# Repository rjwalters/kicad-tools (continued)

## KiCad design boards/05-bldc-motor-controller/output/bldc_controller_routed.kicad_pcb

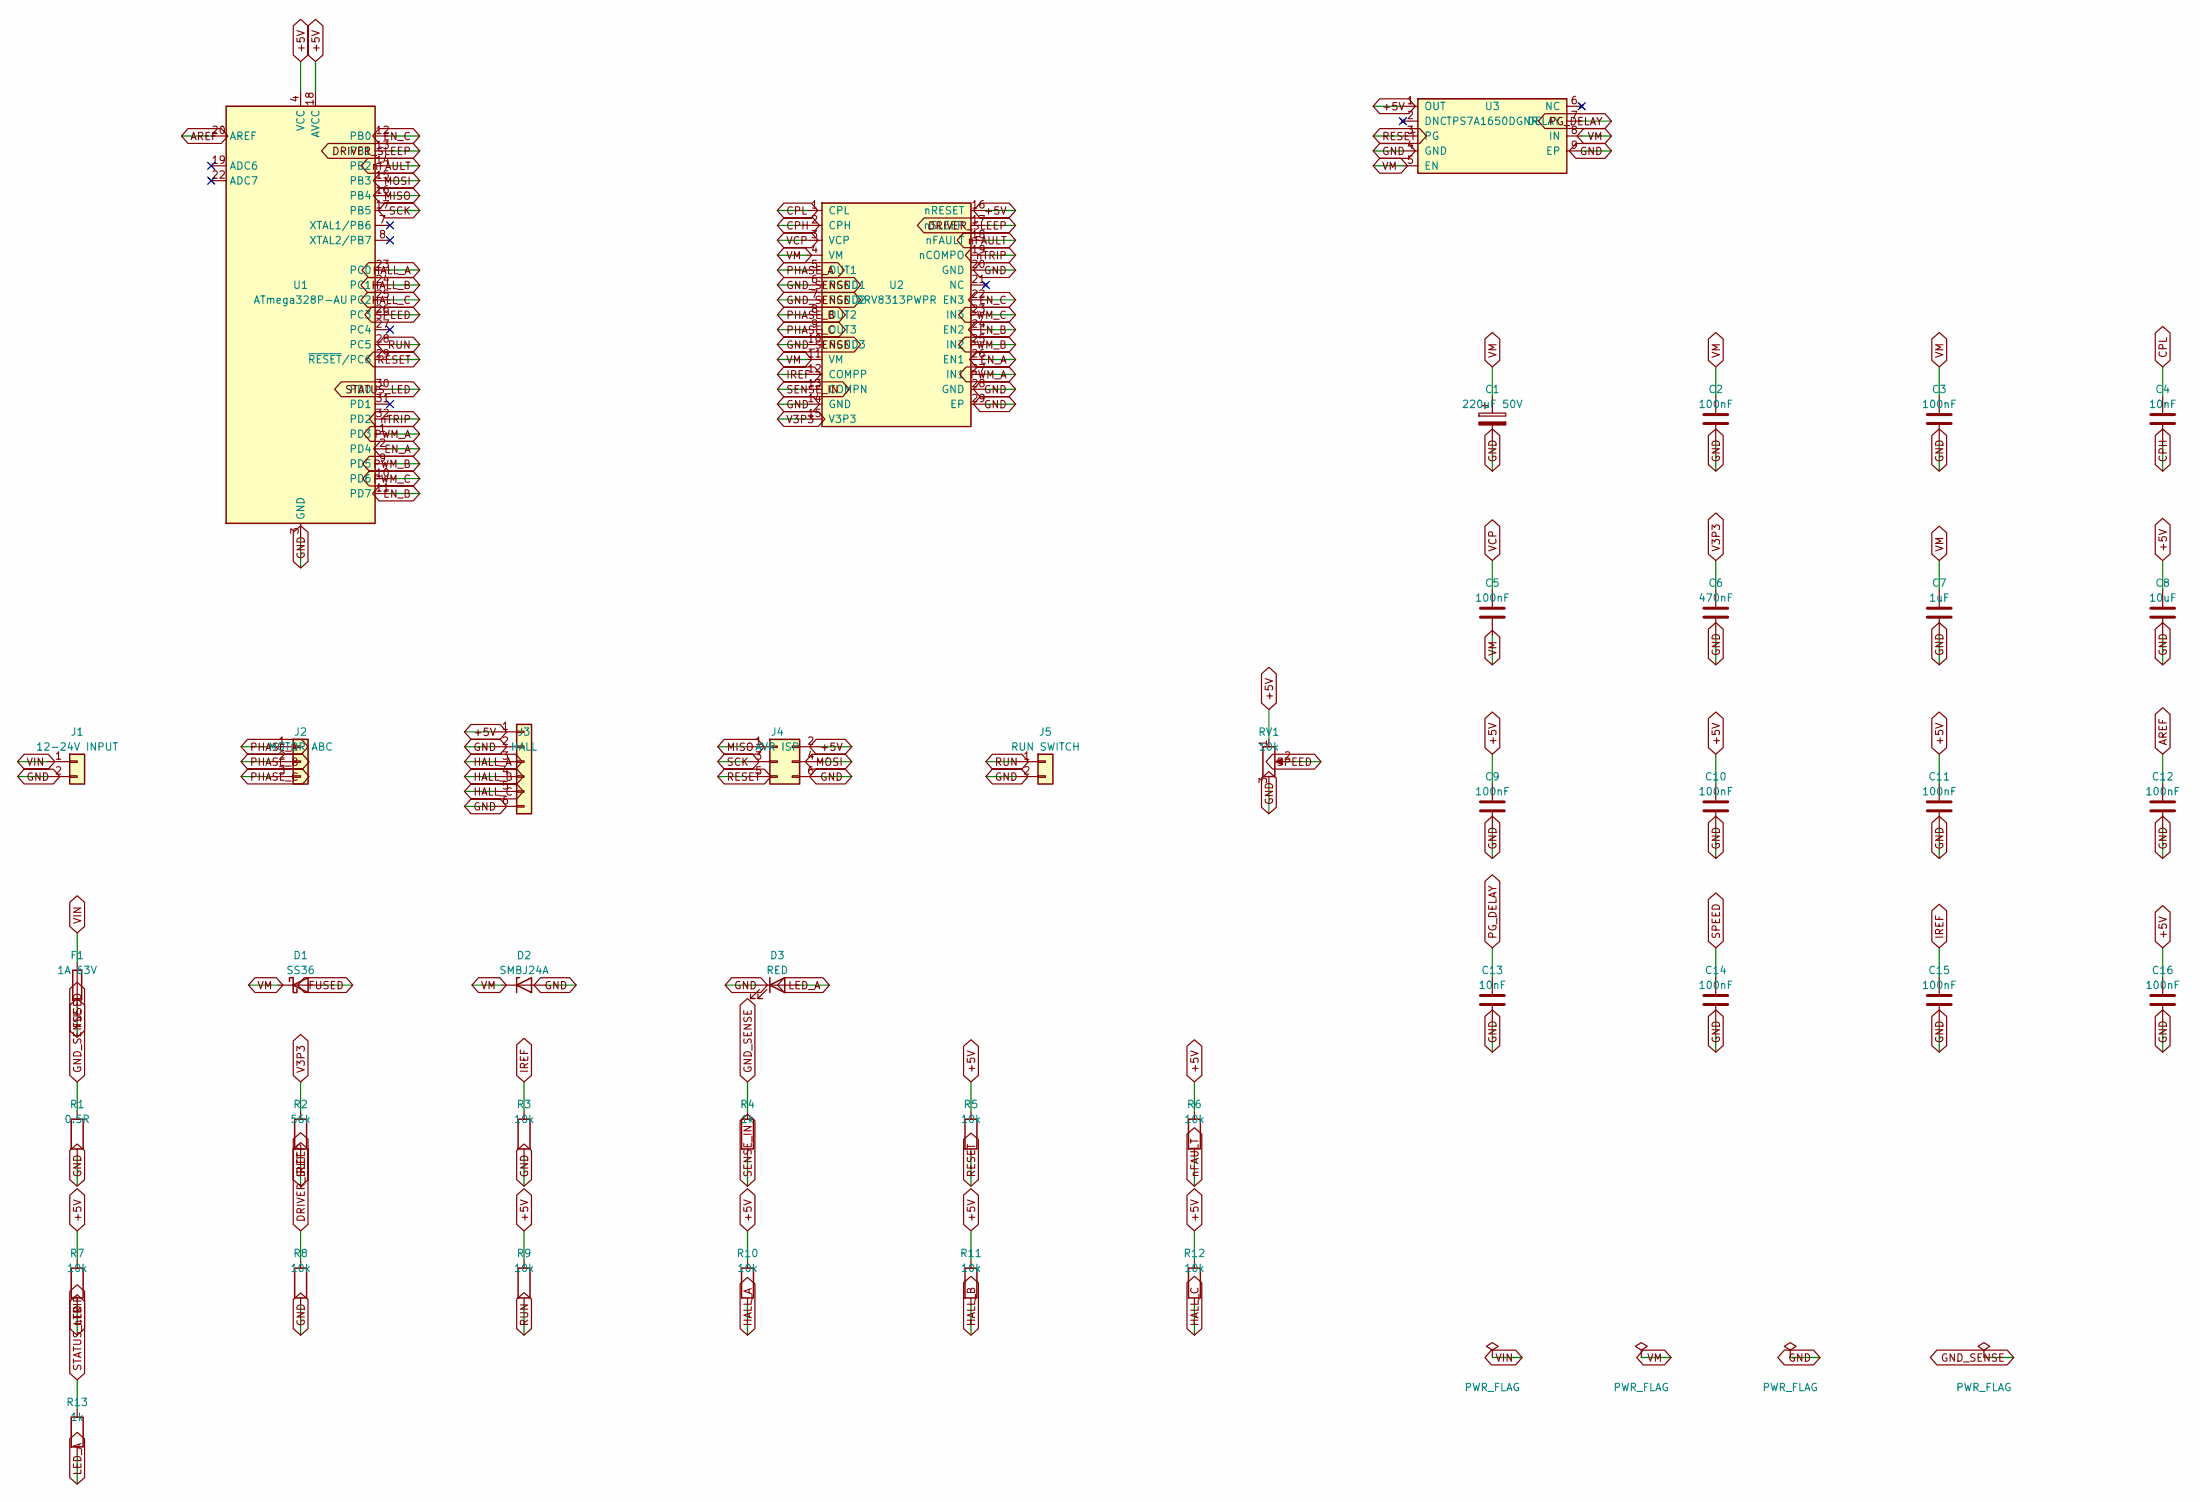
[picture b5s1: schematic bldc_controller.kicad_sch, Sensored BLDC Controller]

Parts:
C1: 220uF 50V; CP_Elec_8x10.5_PolarityMark; MPN EEEFT1H221AP; LCSC C178594
C2, C3, C5, C9, C10, C11, C12, C14, C15, C16: 100nF; C_0805_2012Metric; MPN CC0805KRX7R9BB104; LCSC C49678
C4, C13: 10nF; C_0805_2012Metric; MPN CL21B103KBANNNC; LCSC C1710
C6: 470nF; C_0805_2012Metric; MPN CL21B474KBFNNNE; LCSC C13967
C7: 1uF; C_0805_2012Metric; MPN CL21B105KBFNNNE; LCSC C28323
C8: 10uF; C_0805_2012Metric; MPN CL21A106KAYNNNE; LCSC C15850
D1: SS36; D_SMA; MPN SS36; LCSC C16015
D2: SMBJ24A; D_SMB; MPN SMBJ24A; LCSC C224017
D3: RED; LED_0805_2012Metric; MPN NCD0805R1; LCSC C84256
F1: 1A 63V; Fuse_1206_3216Metric; MPN SF-1206S100-2; LCSC C3167176
J1: 12-24V INPUT; PinHeader_1x02_P2.54mm_Vertical; MPN ZX-PZ2.54-1-2PZZ; LCSC C7501260
J2: MOTOR ABC; PinHeader_1x03_P2.54mm_Vertical; MPN 2.54-1*3P; LCSC C49257
J3: HALL; PinHeader_1x06_P2.54mm_Vertical; MPN 2.54-1*6P; LCSC C37208
J4: AVR ISP; PinHeader_2x03_P2.54mm_Vertical; MPN 2.54-2*3P; LCSC C65114
J5: RUN SWITCH; PinHeader_1x02_P2.54mm_Vertical; MPN ZX-PZ2.54-1-2PZZ; LCSC C7501260
R1: 0.5R; R_2512_6332Metric; MPN WSL2512R5000FEA; LCSC C511023
R2: 56k; R_0805_2012Metric; MPN 0805W8F5602T5E; LCSC C17756
R3, R5, R6, R7, R8, R9, R10, R11, R12: 10k; R_0805_2012Metric; MPN 0805W8F1002T5E; LCSC C17414
R4, R13: 1k; R_0805_2012Metric; MPN 0805W8F1001T5E; LCSC C17513
RV1: 10k; Potentiometer_Bourns_3296W_Vertical; MPN 3296W-1-103LF; LCSC C34846
U1: ATmega328P-AU; TQFP-32_7x7mm_P0.8mm; MPN ATMEGA328P-AU; LCSC C14877
U2: DRV8313PWPR; TI_PWP0028C_EP3.4x9.7_Mask3.1x5.18_ThermalVias; MPN DRV8313PWPR; LCSC C92482
U3: TPS7A1650DGNR; HVSSOP-8-1EP_3x3mm_P0.65mm_EP1.57x1.89mm_ThermalVias; MPN TPS7A1650DGNR; LCSC C468238

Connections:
+5V: C8.1, C9.1, C10.1, C11.1, C16.1, J3.1, J4.2, R5.1, R6.1, R7.1, R9.1, R10.1, R11.1, R12.1, RV1.1, U1.4 (VCC), U1.6 (VCC), U1.18 (AVCC), U2.16 (nRESET), U3.1 (OUT)
AREF: C12.1, U1.20 (AREF)
CPH: C4.2, U2.2 (CPH)
CPL: C4.1, U2.1 (CPL)
DRIVER_SLEEP: R8.1, U1.13 (PB1), U2.17 (nSLEEP)
EN_A: U1.2 (PD4), U2.26 (EN1)
EN_B: U1.11 (PD7), U2.24 (EN2)
EN_C: U1.12 (PB0), U2.22 (EN3)
FUSED: D1.2 (A), F1.2
HALL_A: J3.3, R10.2, U1.23 (PC0)
HALL_B: J3.4, R11.2, U1.24 (PC1)
HALL_C: J3.5, R12.2, U1.25 (PC2)
IREF: C15.1, R2.2, R3.1, U2.12 (COMPP)
LED_A: D3.2 (A), R13.2
MISO: J4.1, U1.16 (PB4)
MOSI: J4.4, U1.15 (PB3)
PG_DELAY: C13.1, U3.7 (DELAY)
PHASE_A: J2.1, U2.5 (OUT1)
PHASE_B: J2.2, U2.8 (OUT2)
PHASE_C: J2.3, U2.9 (OUT3)
PWM_A: U1.1 (PD3), U2.27 (IN1)
PWM_B: U1.9 (PD5), U2.25 (IN2)
PWM_C: U1.10 (PD6), U2.23 (IN3)
RESET: J4.5, R5.2, U1.29 (~RESET/PC6), U3.3 (PG)
RUN: J5.1, R9.2, U1.28 (PC5)
SCK: J4.3, U1.17 (PB5)
SENSE_IN: R4.2, U2.13 (COMPN)
SPEED: C14.1, RV1.2, U1.26 (PC3)
STATUS_LED: R13.1, U1.30 (PD0)
V3P3: C6.1, R2.1, U2.15 (V3P3)
VCP: C5.1, U2.3 (VCP)
nFAULT: R6.2, U1.14 (PB2), U2.18 (nFAULT)
nTRIP: R7.2, U1.32 (PD2), U2.19 (nCOMPO)

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
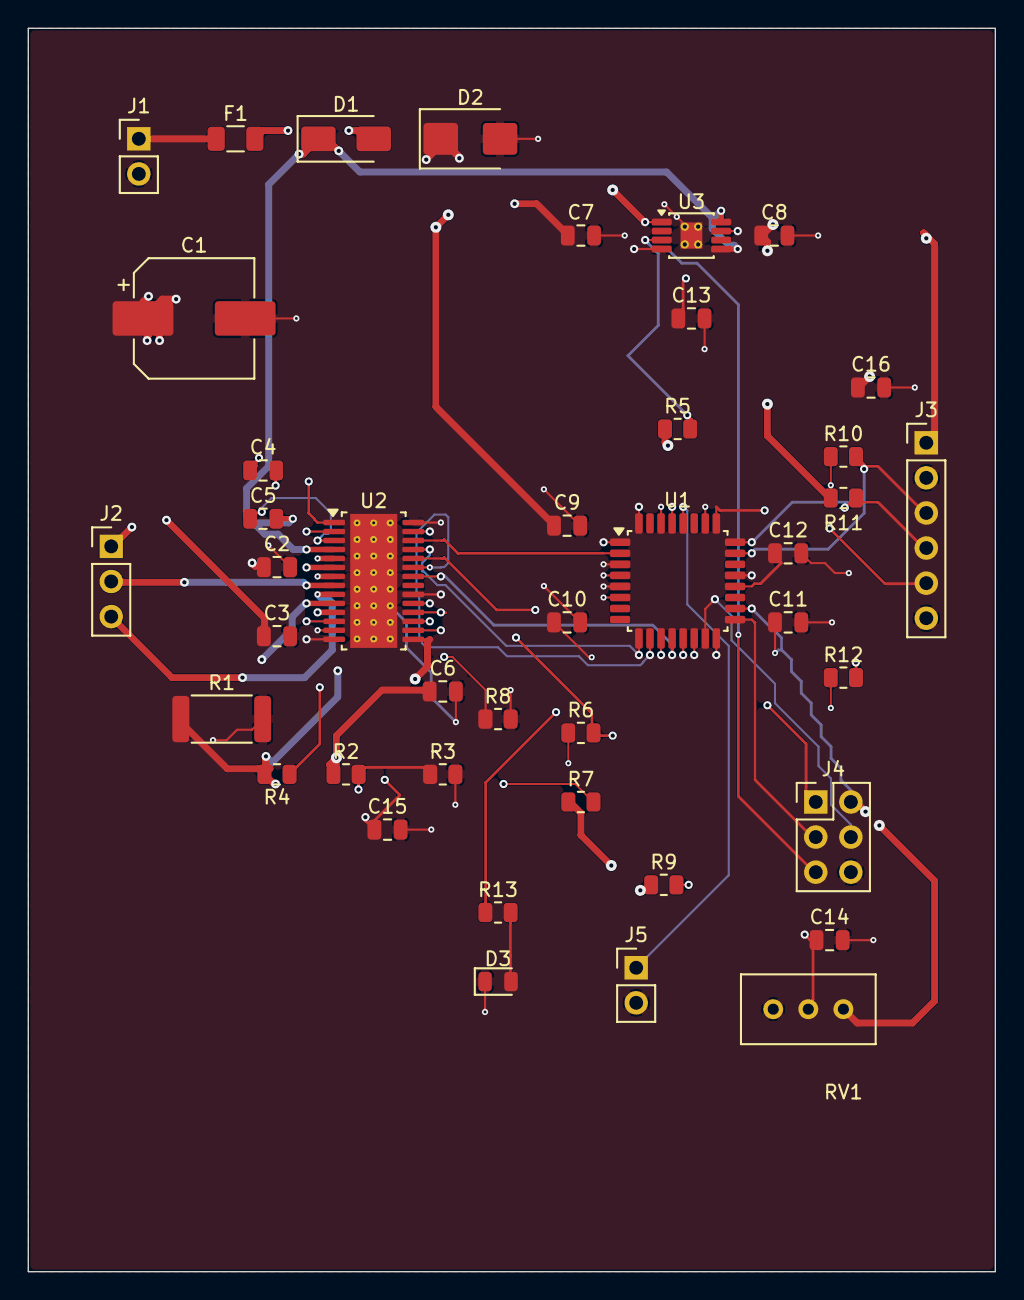
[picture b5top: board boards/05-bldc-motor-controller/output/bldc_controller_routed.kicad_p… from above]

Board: 4 copper layers, 70.0 x 90.0 mm, 42 parts (0 on the bottom side), 37 nets.

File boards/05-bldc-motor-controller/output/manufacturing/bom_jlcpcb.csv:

Comment,Designator,Footprint,LCSC Part #
0.5R,R1,Resistor_SMD:R_2512_6332Metric,C511023
100nF,"C10,C11,C12,C14,C15,C16,C2,C3,C5,C9",Capacitor_SMD:C_0805_2012Metric,C49678
10k,RV1,Potentiometer_THT:Potentiometer_Bourns_3296W_Vertical,C34846
10k,"R10,R11,R12,R3,R5,R6,R7,R8,R9",Resistor_SMD:R_0805_2012Metric,C17414
10nF,"C13,C4",Capacitor_SMD:C_0805_2012Metric,C1710
10uF,C8,Capacitor_SMD:C_0805_2012Metric,C15850
12-24V INPUT,J1,Connector_PinHeader_2.54mm:PinHeader_1x02_P2.54mm_Vertical,C7501260
1A 63V,F1,Fuse:Fuse_1206_3216Metric,C3167176
1k,"R13,R4",Resistor_SMD:R_0805_2012Metric,C17513
1uF,C7,Capacitor_SMD:C_0805_2012Metric,C28323
220uF 50V,C1,board05_revB:CP_Elec_8x10.5_PolarityMark,C178594
470nF,C6,Capacitor_SMD:C_0805_2012Metric,C13967
56k,R2,Resistor_SMD:R_0805_2012Metric,C17756
ATmega328P-AU,U1,Package_QFP:TQFP-32_7x7mm_P0.8mm,C14877
AVR ISP,J4,Connector_PinHeader_2.54mm:PinHeader_2x03_P2.54mm_Vertical,C65114
DRV8313PWPR,U2,board05_revB:TI_PWP0028C_EP3.4x9.7_Mask3.1x5.18_ThermalVias,C92482
HALL,J3,Connector_PinHeader_2.54mm:PinHeader_1x06_P2.54mm_Vertical,C37208
MOTOR ABC,J2,Connector_PinHeader_2.54mm:PinHeader_1x03_P2.54mm_Vertical,C49257
RED,D3,LED_SMD:LED_0805_2012Metric,C84256
RUN SWITCH,J5,Connector_PinHeader_2.54mm:PinHeader_1x02_P2.54mm_Vertical,C7501260
SMBJ24A,D2,Diode_SMD:D_SMB,C224017
SS36,D1,Diode_SMD:D_SMA,C16015
TPS7A1650DGNR,U3,Package_SO:HVSSOP-8-1EP_3x3mm_P0.65mm_EP1.57x1.89mm_ThermalVias,C468238

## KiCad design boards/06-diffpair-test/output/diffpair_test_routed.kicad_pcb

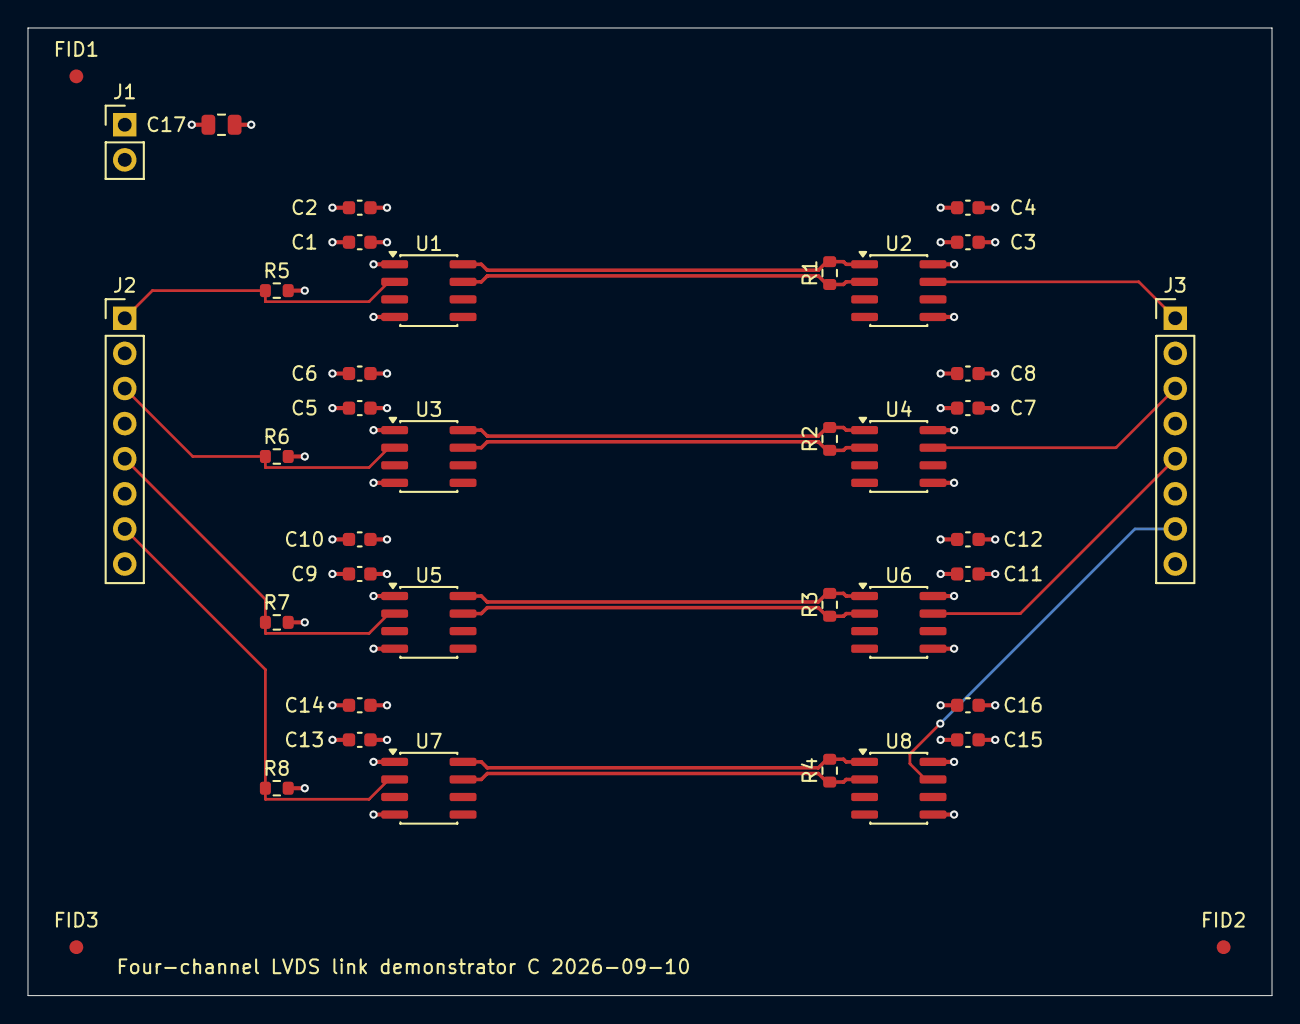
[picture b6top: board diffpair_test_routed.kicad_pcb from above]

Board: 4 copper layers, 90.0 x 70.0 mm, 39 parts (0 on the bottom side), 18 nets.

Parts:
C1, C3, C5, C7, C9, C11, C13, C15: 1nF; C_0603_1608Metric
C2, C4, C6, C8, C10, C12, C14, C16: 100nF; C_0603_1608Metric
C17: 10uF; C_0805_2012Metric
FID1, FID2, FID3: Fiducial; Fiducial_1mm_Mask2mm
J1: 3.3V regulated input; PinHeader_1x02_P2.54mm_Vertical
J2: IN1-4 / GND; PinHeader_1x08_P2.54mm_Vertical
J3: OUT1-4 / GND; PinHeader_1x08_P2.54mm_Vertical
R1, R2, R3, R4: 100; R_0603_1608Metric
R5, R6, R7, R8: 100k; R_0603_1608Metric
U1, U3, U5, U7: SN65LVDS1DR; SOIC-8_3.9x4.9mm_P1.27mm
U2, U4, U6, U8: SN65LVDS2DR; SOIC-8_3.9x4.9mm_P1.27mm

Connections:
+3V3: C1.1, C2.1, C3.1, C4.1, C5.1, C6.1, C7.1, C8.1, C9.1, C10.1, C11.1, C12.1, C13.1, C14.1, C15.1, C16.1, C17.1, J1.1, U1.1 (VCC), U2.8 (VCC), U3.1 (VCC), U4.8 (VCC), U5.1 (VCC), U6.8 (VCC), U7.1 (VCC), U8.8 (VCC)
GND: C1.2, C2.2, C3.2, C4.2, C5.2, C6.2, C7.2, C8.2, C9.2, C10.2, C11.2, C12.2, C13.2, C14.2, C15.2, C16.2, C17.2, J1.2, J2.2, J2.4, J2.6, J2.8, J3.2, J3.4, J3.6, J3.8, R5.2, R6.2, R7.2, R8.2, U1.4 (GND), U2.5 (GND), U3.4 (GND), U4.5 (GND), U5.4 (GND), U6.5 (GND), U7.4 (GND), U8.5 (GND)
IN1: J2.1, R5.1, U1.2 (D)
IN2: J2.3, R6.1, U3.2 (D)
IN3: J2.5, R7.1, U5.2 (D)
IN4: J2.7, R8.1, U7.2 (D)
LVDS1_N: R1.2, U1.8 (Z), U2.1 (B)
LVDS1_P: R1.1, U1.7 (Y), U2.2 (A)
LVDS2_N: R2.2, U3.8 (Z), U4.1 (B)
LVDS2_P: R2.1, U3.7 (Y), U4.2 (A)
LVDS3_N: R3.2, U5.8 (Z), U6.1 (B)
LVDS3_P: R3.1, U5.7 (Y), U6.2 (A)
LVDS4_N: R4.2, U7.8 (Z), U8.1 (B)
LVDS4_P: R4.1, U7.7 (Y), U8.2 (A)
OUT1: J3.1, U2.7 (R)
OUT2: J3.3, U4.7 (R)
OUT3: J3.5, U6.7 (R)
OUT4: J3.7, U8.7 (R)

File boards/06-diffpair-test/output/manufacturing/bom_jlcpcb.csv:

Comment,Designator,Footprint,LCSC Part #
100,"R1,R2,R3,R4",Resistor_SMD:R_0603_1608Metric,C22775
100k,"R5,R6,R7,R8",Resistor_SMD:R_0603_1608Metric,C25803
100nF,"C10,C12,C14,C16,C2,C4,C6,C8",Capacitor_SMD:C_0603_1608Metric,C14663
10uF,C17,Capacitor_SMD:C_0805_2012Metric,C15850
1nF,"C1,C11,C13,C15,C3,C5,C7,C9",Capacitor_SMD:C_0603_1608Metric,C1588
3.3V regulated input,J1,Connector_PinHeader_2.54mm:PinHeader_1x02_P2.54mm_Vertical,C492401
IN1-4 / GND,J2,Connector_PinHeader_2.54mm:PinHeader_1x08_P2.54mm_Vertical,C492407
OUT1-4 / GND,J3,Connector_PinHeader_2.54mm:PinHeader_1x08_P2.54mm_Vertical,C492407
SN65LVDS1DR,"U1,U3,U5,U7",Package_SO:SOIC-8_3.9x4.9mm_P1.27mm,C2671256
SN65LVDS2DR,"U2,U4,U6,U8",Package_SO:SOIC-8_3.9x4.9mm_P1.27mm,C2671054

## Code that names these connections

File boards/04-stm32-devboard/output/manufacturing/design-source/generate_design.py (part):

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The design includes:
- LDO voltage regulator (5V to 3.3V)
- STM32F103C8T6 MCU (LQFP-48) with full power, decoupling and reset wiring
- 8MHz HSE crystal oscillator on PD0/PD1
- SWD debug header (PA13/PA14/PB3/NRST)
- User LED indicator on PB12 (active-low)

Usage:
    python generate_design.py [output_dir]
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    print("   C12-C15 (100nF) + C16 (4.7uF) bypass caps")

    # =========================================================================
    # Section 4: Crystal Oscillator (8MHz) - connects to MCU PD0/PD1
    # =========================================================================
    print("\n4. Adding 8MHz crystal oscillator...")

    # Place crystal to the LEFT of the MCU, where PD0 (pin 5, OSC_IN) and PD1
    # (pin 6, OSC_OUT) emerge.  PD0 is at (MCU_X - 17.78, MCU_Y - 22.86) =
    # (192.22, 97.14) and PD1 at (192.22, 99.68) in screen coords.  Place the
    # crystal block well to the left so its IN/OUT labels align cleanly.
    # y=150 keeps the crystal's horizontal OSC_IN/OSC_OUT stubs off the C2/C3
    # row (y=100), which they previously crossed (Issue #8005).
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    # to add it manually -- see issues #3149 AC #2 and #3468).
    xtal.connect_to_rails(gnd_rail_y=RAIL_GND)

    # Wire crystal IN/OUT to OSC_IN / OSC_OUT labels (on stubs).  Labels at the
    # MCU side are added below when we wire the MCU pins.
    in_pos = xtal.port("IN")
    out_pos = xtal.port("OUT")
    sch.add_wire(in_pos, (in_pos[0] - 10, in_pos[1]))
    sch.add_label("OSC_IN", in_pos[0] - 10, in_pos[1], rotation=0)
    sch.add_wire(out_pos, (out_pos[0] + 10, out_pos[1]))
    sch.add_label("OSC_OUT", out_pos[0] + 10, out_pos[1], rotation=0)
    print("   Added OSC_IN and OSC_OUT labels at crystal")

    # =========================================================================
    # Section 5: Debug Header (SWD)
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    # (1=VCC, 2=SWDIO, 3=GND, 4=SWCLK, 5=GND, 6=NRST), so we drive every
    # pin explicitly to reconcile schematic<->PCB drift pad-for-pad (issue
    # #3765).  Signal pins 2/3/4/5 carry their net labels via ``pin_nets``
    # (each emits a label stub the MCU-side SWDIO/SWCLK/SWO/NRST labels
    # unify with); the power/ground pins 1 and 6 are wired to the +3.3V
    # and GND rails directly below (NOT via ``connect_to_rails``, which
    # assumes the built-in pin-1-VCC / pin-3-GND positions).
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    print("\n6. Wiring MCU peripheral signals...")

    # Helper: route a short stub from a left-side MCU pin out to a label.
    # Left-side pins (PA0 family on the right, the rest on the left) emerge
    # along x=MCU_X-17.78, so the stub goes -10mm to the left.
    def _label_left_pin(pin_name: str, label_text: str, stub_len: float = -8) -> None:
        pos = mcu.pin_position(pin_name)
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        sch.add_label(label_text, pos[0] + stub_len, pos[1], rotation=0)

    # Oscillator inputs (left side of symbol)
    _label_left_pin("PD0", "OSC_IN")
    _label_left_pin("PD1", "OSC_OUT")
    print("   PD0 -> OSC_IN, PD1 -> OSC_OUT")

    # Reset (left side)
    _label_left_pin("NRST", "NRST")
    print("   NRST -> NRST (reset header pin)")

    # SWD signals (right side of symbol -- PA13, PA14; left side -- PB3)
    _label_right_pin("PA13", "SWDIO")
    _label_right_pin("PA14", "SWCLK")
    _label_left_pin("PB3", "SWO")
    print("   PA13 -> SWDIO, PA14 -> SWCLK, PB3 -> SWO")

    # User LED on PB12 (left side, lower half).  Active-low: MCU sinks current.
    _label_left_pin("PB12", "USER_LED")
    print("   PB12 -> USER_LED")

    # No-connect markers on every MCU pin we don't drive.  Without these the
    # internal `Schematic.validate()` flags ~30 "pin not connected" errors and
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        # Signals we explicitly wire below
        "NRST",
        "BOOT0",
        "PD0",
        "PD1",
        "PA13",
        "PA14",
        "PB3",
        "PB12",
    }
    _nc_count = 0
    for p in mcu.symbol_def.pins:
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    print("   R2 (10k) BOOT0 pull-down to GND (via create_gpio_pull_resistor)")

    # =========================================================================
    # Section 7: User LED (driven by MCU PB12, active-low)
    # =========================================================================
    print("\n7. Adding user LED (driven by MCU PB12)...")

    # LED + current-limiting resistor, placed and wired manually (NOT via
    # LEDIndicator) so the schematic matches the PCB's canonical pad-for-pad
    # net model (the routed-layout source of truth) exactly (issue #3765):
    #
    #   +3.3V --[R1]-- LED_K --[D1]-- USER_LED --> MCU PB12 (active-low)
    #
    # PCB pad assignment we must reproduce:
    #   R1.pad1 = +3.3V,  R1.pad2 = LED_K
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    # Both symbols are placed vertical (rotation=90) and spaced apart; every
    # pad gets a short stub + global net label, so the per-pad net binding is
    # independent of the exact pad geometry (no fragile cross-body diagonal
    # wires).  The intermediate LED_K node is realized by labelling BOTH
    # R1.pad2 and D1.pad1 ``LED_K`` -- KiCad unifies same-named global labels.
    r1 = sch.add_symbol(
        "Device:R",
        x=265,
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
    # R1.pad1 -> +3.3V, R1.pad2 -> LED_K
    _label_pad(r1, "1", "+3.3V", 0.0, -8.0)
    _label_pad(r1, "2", "LED_K", 0.0, 8.0)
    # D1.pad1 (K) -> LED_K, D1.pad2 (A) -> USER_LED.  Per the PCB footprint
    # pad order (pad1=anode net LED_K, pad2=cathode net USER_LED), wired by
    # pad number: the Device:LED symbol's pad1 is "K" / pad2 is "A".
    _label_pad(d1, "1", "LED_K", 0.0, 8.0)
    _label_pad(d1, "2", "USER_LED", 0.0, -8.0)
    print("   R1/D1 wired: +3.3V -> R1 -> LED_K -> D1 -> USER_LED (MCU PB12)")

    # =========================================================================
    # Section 8: Design Notes
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
    sch.add_text(
        "STM32F103C8T6 Pin Assignments:\n"
        "  PA13 = SWDIO    (pin 34)\n"
        "  PA14 = SWCLK    (pin 37)\n"
        "  PB3  = SWO      (pin 39)\n"
        "  NRST = Reset    (pin 7)\n"
        "  PD0  = OSC_IN   (pin 5, HSE)\n"
        "  PD1  = OSC_OUT  (pin 6, HSE)\n"
        "  PB12 = USER_LED (pin 25, active-low)\n"
        "  BOOT0 pulled low via R2 (10k) for flash boot\n"
        "  HSE: 8MHz crystal Y1 with 20pF load caps C10/C11\n"
        "  Decoupling: C12-C15 (100nF) per VDD pin, C16 (4.7uF) bulk",
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    # Crystal section: above the MCU's top edge.  Y1 sits between the LDO
    # and MCU horizontally, with OSC_IN/OSC_OUT load caps below it.
    # OSC_IN/OSC_OUT escape through the open space above the MCU's left
    # edge (PD0=pin 5, PD1=pin 6).
    #
    # Y1 sits at x=+23, not +22 (Issue #7204): the stock HC49-4H courtyard is
    # a stadium reaching 6.03 mm either side of the footprint origin, and at
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        35: "GND",  # VSS
        47: "GND",  # VSS
        # Signals
        5: "OSC_IN",  # PD0
        6: "OSC_OUT",  # PD1
        7: "NRST",  # NRST
        25: "USER_LED",  # PB12
        34: "SWDIO",  # PA13
        37: "SWCLK",  # PA14
        39: "SWO",  # PB3
        44: "BOOT0",  # BOOT0 (pulled low via R2)
    }
    parts.append(generate_lqfp48("U2", U2_POS, "STM32F103C8T6", mcu_pin_nets))
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    print(f"   C16 (4.7uF bulk decoupling) at {C16_POS}")

    # R1: LED current-limiting resistor (3.3V -> LED_K).  D1 pulls LED_K
    # toward USER_LED net; when MCU PB12 sinks current the LED illuminates.
    parts.append(generate_resistor_0805("R1", R1_POS, "330R", "+3.3V", "LED_K"))
    print(f"   R1 (330R) at {R1_POS}")

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    """Relieve fine-pitch hole-to-hole via crowding (issue #4408).

    The fresh deterministic route escapes three adjacent LQFP-48 west pins
    (OSC_OUT / NRST / GND) through in-pad micro-vias stacked at the 0.5 mm pin
    pitch.  Two of the resulting drill pairs measure 0.350 mm edge-to-edge --
    below the ``jlcpcb-tier1`` 0.500 mm ``min_hole_to_hole_mm`` floor -- so a
    fresh regen previously FAILED ``kct check --mfr jlcpcb-tier1`` with 2
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
        # Step 5.5: Fix the OSC_OUT escape-stub short (#3797) -- the fresh
        # deterministic route drops the OSC_OUT B.Cu escape straight into the
        # U2.5 OSC_IN pad, shorting the two crystal pins.  This deterministic
        # post-route surgery re-aims that single B.Cu hop off the OSC_IN pad
        # column (the programmatic form of #3785's hand fix), so a fresh regen
        # is copper-LVS clean.  Must run after route_pcb (which emits the
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        # mfr-floor-driven pass relocates the offending (middle NRST) via onto a
        # clearance-safe escape node and re-bonds it with connectivity stubs,
        # back-porting the artifact-only #4017 nudge into the recipe so a fresh
        # regen is tier1-clean by construction.  Must run AFTER stitch_pcb +
        # tie_power_pads (so it sees every via) and BEFORE quantize_escapes (so
        # any stub is 45-quantized) / fill_zones (so the re-pour backs off the
        # relocated via).
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        print("  - U1: MCP1825S-3302E/DB LDO (5V to 3.3V)")
        print("  - U2: STM32F103C8T6 MCU (LQFP-48, 0.5mm pitch)")
        print("  - C1-C3: LDO decoupling capacitors")
        print("  - Y1: 8MHz crystal oscillator (HSE on PD0/PD1)")
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
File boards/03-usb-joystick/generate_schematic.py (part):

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        btn_net="JOY_BTN",
        # Filter + pull-up are emitted explicitly below (see note above);
        # disable the factory's series filter so it labels the raw
        # connector pins JOY_X / JOY_Y / JOY_BTN directly.
        filter_cutoff_hz=None,
        btn_pullup=None,
    )
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        "32": "GND",
    }

    # Joystick pin labels (VCC/GND/JOY_X/JOY_Y/JOY_BTN) are emitted by
    # ``create_analog_joystick`` in Section 3 — no inline wiring needed here.

    # Wire MCU pins with global labels
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
    # Wire crystal pins (load caps already wired internally by the block).
    # Connect the load-cap ground bus to the GND rail and label IN/OUT for
    # routing back to the MCU XTAL1/XTAL2 pins.
    print("   Wiring Crystal (Y1) pins...")
    # Label the load-cap ground bus as GND so C5/C6 pad 2 resolve to the
    # GND net (matches PCB C5-2/C6-2 = GND).  ``connect_to_rails`` only
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    # the load caps on auto-named ``Net-(C5-2)`` nets and broke LVS
    # (issue #3764).
    add_pin_label(sch, xtal_block.port("GND"), "GND", direction="right")
    add_pin_label(sch, xtal_block.port("IN"), "XTAL1", direction="left")
    print("      IN -> XTAL1")
    add_pin_label(sch, xtal_block.port("OUT"), "XTAL2", direction="right")
    print("      OUT -> XTAL2")

    # Wire buttons to MCU GPIO pins
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
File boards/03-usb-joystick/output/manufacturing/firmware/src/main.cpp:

#include <Arduino.h>
#include <Joystick.h>
#include <avr/io.h>

// Read silicon ports directly: the board does not use Leonardo header mapping.
// U1.41 PF0/ADC0 = X, U1.40 PF1/ADC1 = Y.
// U1.18/19/20/21/25 PD0..4 = BTN1..4 and joystick pushbutton.
static Joystick_ joystick(0x03, JOYSTICK_TYPE_JOYSTICK, 5, 0,
                          true, true, false, false, false, false,
                          false, false, false, false, false);
static uint8_t debounce[5] = {};
static uint8_t pressed = 0;

static uint16_t convertADC() {
    ADCSRA |= _BV(ADSC);
    while (ADCSRA & _BV(ADSC)) {}
    return ADC;
}

static uint16_t readAxis(uint8_t channel) {
    ADMUX = _BV(REFS0) | channel; // AVCC reference; right-adjusted 10-bit result.
    ADCSRB &= ~_BV(MUX5);
    (void)convertADC(); // Discard after mux change so the sample capacitor settles.
    return convertADC();
}

static_assert(F_CPU == 8000000UL, "Board revision B uses an 8 MHz crystal");

void setup() {
    DDRD &= ~0x1f;
    PORTD &= ~0x1f; // The PCB provides external 10k pull-ups.
    DDRF &= ~(_BV(PF0) | _BV(PF1));
    PORTF &= ~(_BV(PF0) | _BV(PF1));
    DIDR0 |= _BV(ADC0D) | _BV(ADC1D);
    ADCSRA = _BV(ADEN) | _BV(ADPS2) | _BV(ADPS1); // 125 kHz ADC.
    joystick.setXAxisRange(0, 1023);
    joystick.setYAxisRange(0, 1023);
    joystick.begin(false);
}

void loop() {
    USBDevice.poll(); // Restore clocks before cadence checks or endpoint traffic.
    static uint32_t previous = 0;
    const uint32_t now = millis();
    if (uint32_t(now - previous) < 2) return;
    previous = now;
    const uint8_t raw = uint8_t(~PIND) & 0x1f;
    for (uint8_t i = 0; i < 5; ++i) {
        // Saturating integrator: a stable change takes five 2 ms samples.
        if (raw & _BV(i)) {
            if (debounce[i] < 5) ++debounce[i];
        } else if (debounce[i] > 0) {
            --debounce[i];
        }
        if (debounce[i] == 5) pressed |= _BV(i);
        if (debounce[i] == 0) pressed &= ~_BV(i);
        joystick.setButton(i, bool(pressed & _BV(i)));
    }
    joystick.setXAxis(readAxis(0));
    joystick.setYAxis(readAxis(1));
    if (USBDevice.configured() && !USBDevice.isSuspended()) joystick.sendState();
}
